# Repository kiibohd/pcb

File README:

PCB and PCB Related Bits

In general kicad is used for projects.
A project will be explicit if another program is required to view.

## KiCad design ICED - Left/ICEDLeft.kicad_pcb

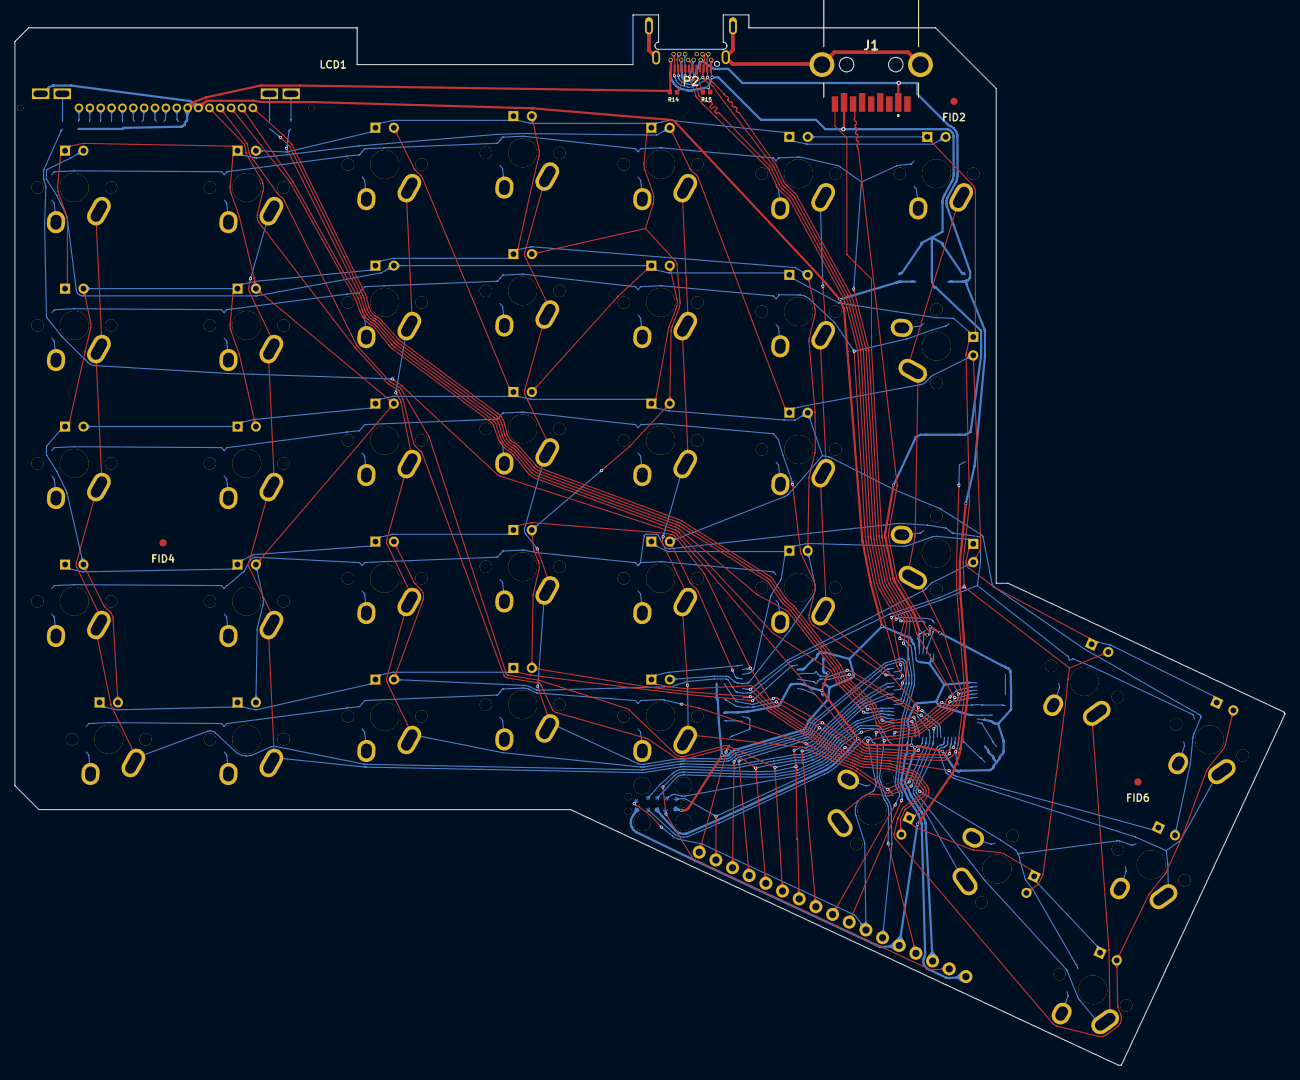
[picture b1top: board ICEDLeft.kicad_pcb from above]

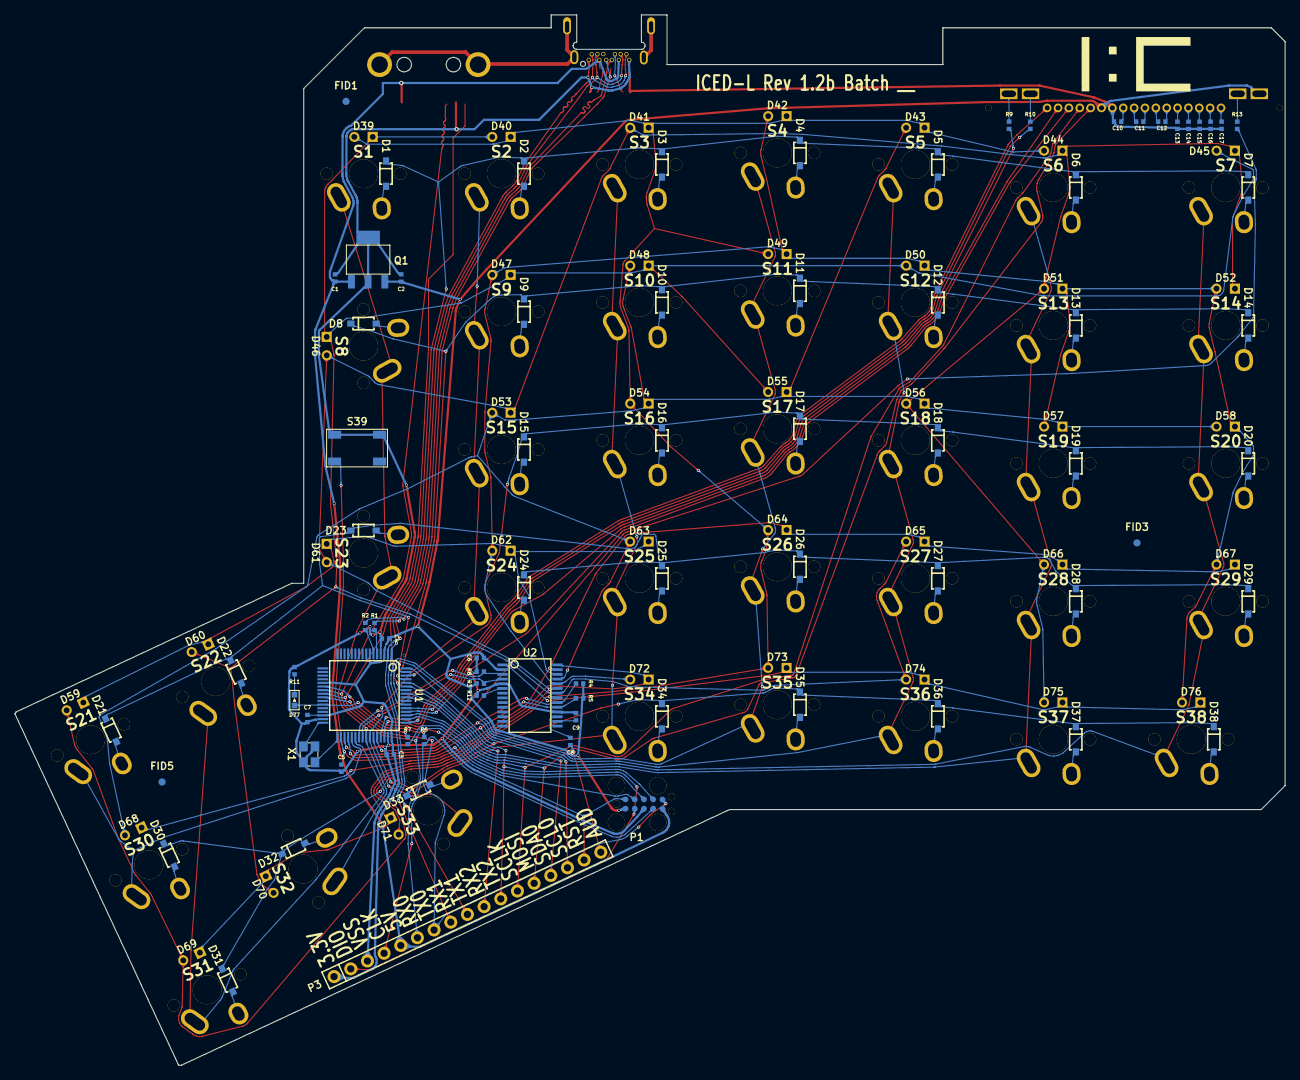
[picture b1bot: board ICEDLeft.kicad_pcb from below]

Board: 2 copper layers, 175.4 x 145.0 mm, 164 parts (80 on the bottom side), 115 nets.

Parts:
C1, C2, C6, C10, C11, C12, C13, C14, C15, C16, C17: 1uF; SMD-1005
C3, C4, C5, C7, C9: 0.1uF; SMD-1005
C8: 0.22uF; SMD-1005
D1, D2, D3, D4, D5, D6, D7, D8, D9, D10, D11, D12, D13, D14, D15, D16, D17, D18, D19, D20, D21, D22, D23, D24, D25, D26, D27, D28, D29, D30, D31, D32, D33, D34, D35, D36, D37, D38: DIODE; SOT123-DIODE
D39, D40, D41, D42, D43, D44, D45, D46, D47, D48, D49, D50, D51, D52, D53, D54, D55, D56, D57, D58, D59, D60, D61, D62, D63, D64, D65, D66, D67, D68, D69, D70, D71, D72, D73, D74, D75, D76: LED; INSW_LEDS_REG
D77: LED; LED-0603
FID1, FID2, FID3, FID4, FID5, FID6: >VALUE; FID
IC_LOGO: IC_LOGO
J1: 692122030100
LCD1: NHD-C12832A1Z
P1: FLASH_HDR; JLINK_NEEDLE
P2: USBC; USB_C_MIDMOUNT_TH_IMPCUT
P3: CONN_17; HEADER_1x17
Q1: TC1264; SOT-223
R1, R2, R13: 33; SMD-1005
R3, R4, R5: 4.7k; SMD-1005
R6, R7: 100; SMD-1005
R8: 100k; SMD-1005
R9, R10: 66.5; SMD-1005
R11: 1k; SMD-1005
R12: 20k; SMD-1005
R14, R15: 5.1k; SMD-1005
S1, S2, S3, S4, S5, S6, S7, S8, S9, S10, S11, S12, S13, S14, S15, S16, S17, S18, S19, S20, S21, S22, S23, S24, S25, S26, S27, S28, S29, S30, S31, S32, S33, S34, S35, S36, S37, S38: SW; MXALPS
S39: TAC_SWITCH; TACT_5.2x5.2
U1: MK20DX256VLH7; LQFP64
U2: IS31FL3731C; SSOP-28
X1: CRYSTAL; NX3225SA

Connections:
+5V: C1.1, J1.1, P1.5, P2.4, P2.9, P2.16, P2.21, P3.5, Q1.1
/Col1: S21.1, S30.1, U1.37
/Col2: S22.1, S31.1, U1.38
/Col3: S1.1, S8.1, S23.1, S32.1, U1.41
/Col4: S2.1, S9.1, S15.1, S24.1, S33.1, U1.42
/Col5: S3.1, S10.1, S16.1, S25.1, S34.1, U1.43
/Col6: S4.1, S11.1, S17.1, S26.1, S35.1, U1.54
/Col7: S5.1, S12.1, S18.1, S27.1, S36.1, U1.55
/Col8: S6.1, S13.1, S19.1, S28.1, S37.1, U1.56
/Col9: S7.1, S14.1, S20.1, S29.1, S38.1, U1.57
/GND: J1.MH1, J1.MH2, P2.25
/Row1: D1.2, D2.2, D3.2, D4.2, D5.2, D6.2, D7.2, U1.58
/Row2: D8.2, D9.2, D10.2, D11.2, D12.2, D13.2, D14.2, U1.61
/Row3: D15.2, D16.2, D17.2, D18.2, D19.2, D20.2, U1.62
/Row4: D21.2, D22.2, D23.2, D24.2, D25.2, D26.2, D27.2, D28.2, D29.2, U1.63
/Row5: D30.2, D31.2, D32.2, D33.2, D34.2, D35.2, D36.2, D37.2, D38.2, U1.64
/ledmatrix/CA1: D39.2, D40.1, D41.1, D42.1, D43.1, D44.2, D49.2, D54.2, D59.2, D64.2, D69.2, D73.2, U2.21
/ledmatrix/CA2: D39.1, D40.2, D45.2, D46.1, D47.1, D48.1, D50.2, D55.2, D60.2, D65.2, D70.2, D74.2, U2.22
/ledmatrix/CA3: D41.2, D44.1, D45.1, D46.2, D51.2, D52.1, D53.1, D56.2, D61.2, D66.2, D71.2, D75.2, U2.23
/ledmatrix/CA4: D42.2, D47.2, D49.1, D50.1, D51.1, D52.2, D57.2, D58.1, D62.2, D67.2, D72.2, D76.2, U2.24
/ledmatrix/CA5: D43.2, D48.2, D53.2, D54.1, D55.1, D56.1, D57.1, D58.2, D63.2, D68.2, U2.25
/ledmatrix/CA6: D59.1, D60.1, D61.1, D62.1, D63.1, U2.26
/ledmatrix/CA7: D64.1, D65.1, D66.1, D67.1, D68.1, U2.27
/ledmatrix/CA8: D69.1, D70.1, D71.1, D72.1, U2.28
/ledmatrix/CA9: D73.1, D74.1, D75.1, D76.1, U2.1
/mcu/A0: LCD1.17, U1.52
/mcu/AUD: C8.2, P3.17
/mcu/INTB: R3.2, U1.40, U2.4
/mcu/LCD_KB: R9.2, U1.46
/mcu/LCD_KG: R10.2, U1.45
/mcu/LCD_KR: R13.2, U1.44
/mcu/MCU_RESET: C5.1, P1.10, P3.16, S39.2, U1.34
/mcu/MOSI: LCD1.15, P3.13, U1.51
/mcu/PTA5: D77.1, P1.9, U1.27
/mcu/RST: LCD1.18, U1.53
/mcu/RX0: J1.6, P1.8, P3.6, U1.23
/mcu/RX1: P2.3, P2.10, P2.15, P2.22, P3.8, U1.2
/mcu/RX2: P3.10, U1.59
/mcu/SCL0: P3.15, R4.2, U1.35, U2.20
/mcu/SCLK: LCD1.16, P3.12, U1.50
/mcu/SDA0: P3.14, R5.2, U1.36, U2.19
/mcu/SDB: R8.2, U1.39, U2.3
/mcu/SS1: LCD1.19, U1.49
/mcu/SWD_CLK: P1.4, P3.4, R6.2
/mcu/SWD_DIO: P1.2, P3.2, R7.2
/mcu/TX0: J1.5, P1.6, P3.7, U1.24
/mcu/TX1: P2.2, P2.11, P2.14, P2.23, P3.9, U1.1
/mcu/TX2: P1.7, P3.11, U1.60
/mcu/USB_DM: P2.7, P2.19, R2.1
/mcu/USB_DP: P2.6, P2.18, R1.1
unnamed: C8.1, U2.17
unnamed: C9.1, U2.16
unnamed: C10.1, LCD1.12
unnamed: C11.1, LCD1.11
unnamed: C11.2, LCD1.10
unnamed: C12.1, LCD1.9
unnamed: C12.2, LCD1.8
unnamed: C13.2, LCD1.7
unnamed: C14.2, LCD1.6
unnamed: C15.2, LCD1.5
unnamed: C16.2, LCD1.4
unnamed: C17.2, LCD1.3
unnamed: D1.1, S1.2
unnamed: D2.1, S2.2
unnamed: D3.1, S3.2
unnamed: D4.1, S4.2
unnamed: D5.1, S5.2
unnamed: D6.1, S6.2
unnamed: D7.1, S7.2
unnamed: D8.1, S8.2
unnamed: D9.1, S9.2
unnamed: D10.1, S10.2
unnamed: D11.1, S11.2
unnamed: D12.1, S12.2
unnamed: D13.1, S13.2
unnamed: D14.1, S14.2
unnamed: D15.1, S15.2
unnamed: D16.1, S16.2
unnamed: D17.1, S17.2
unnamed: D18.1, S18.2
unnamed: D19.1, S19.2
unnamed: D20.1, S20.2
unnamed: D21.1, S21.2
unnamed: D22.1, S22.2
unnamed: D23.1, S23.2
unnamed: D24.1, S24.2
unnamed: D25.1, S25.2
unnamed: D26.1, S26.2
unnamed: D27.1, S27.2
unnamed: D28.1, S28.2
unnamed: D29.1, S29.2
unnamed: D30.1, S30.2
unnamed: D31.1, S31.2
unnamed: D32.1, S32.2
unnamed: D33.1, S33.2
unnamed: D34.1, S34.2
unnamed: D35.1, S35.2
unnamed: D36.1, S36.2
unnamed: D37.1, S37.2
unnamed: D38.1, S38.2
unnamed: D77.2, R11.1
unnamed: LCD1.2, R13.1
unnamed: LCD1.20, R10.1
unnamed: LCD1.21, R9.1
unnamed: P2.5, R15.1
unnamed: P2.17, R14.1
unnamed: R1.2, U1.5
unnamed: R2.2, U1.6
unnamed: R6.1, U1.22
unnamed: R7.1, U1.25
unnamed: R12.1, U2.6
unnamed: U1.32, X1.1
unnamed: U1.33, X1.3
VDD: C2.1, C3.1, C4.1, C6.2, C7.1, LCD1.1, LCD1.14, P1.1, P3.1, Q1.3, R3.1, R4.1, R5.1, U1.3, U1.7, U1.8, U1.21, U1.30, U1.48, U2.2
VSS: C1.2, C2.2, C3.2, C4.2, C5.2, C6.1, C7.2, C9.2, C10.2, C13.1, C14.1, C15.1, C16.1, C17.1, J1.4, LCD1.13, P1.3, P2.1, P2.12, P2.13, P2.24, P3.3, Q1.2, R8.1, R11.2, R12.2, R14.2, R15.2, S39.3, S39.4, U1.4, U1.31, U1.47, U2.5, U2.18, X1.2, X1.4

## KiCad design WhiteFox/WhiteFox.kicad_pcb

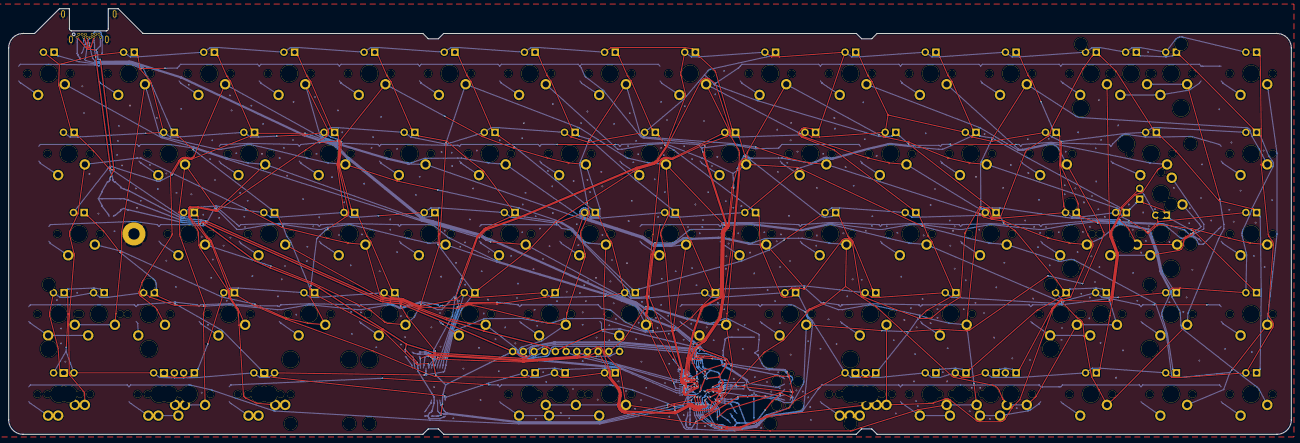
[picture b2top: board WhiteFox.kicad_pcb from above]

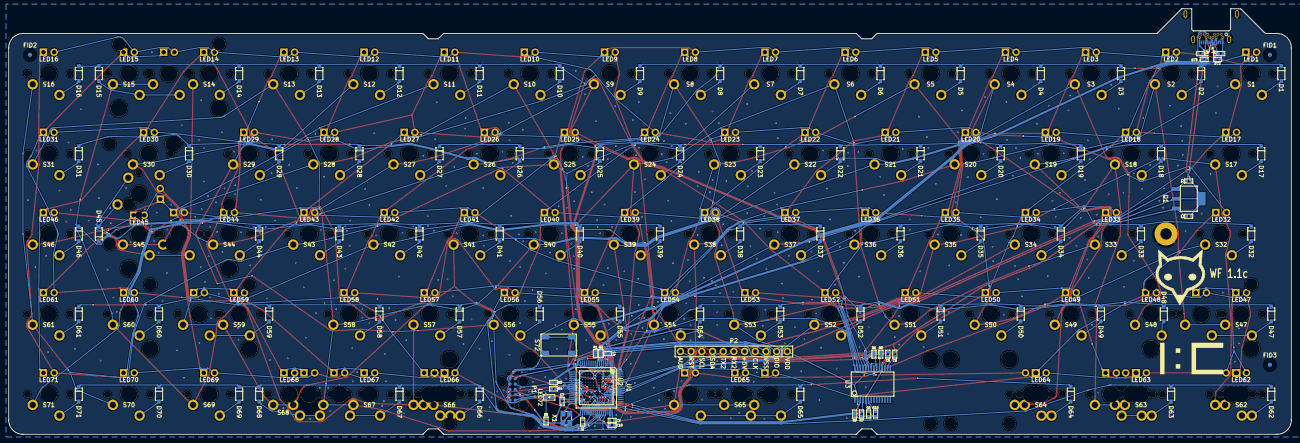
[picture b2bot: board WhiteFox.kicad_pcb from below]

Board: 2 copper layers, 304.8 x 101.1 mm, 297 parts (109 on the bottom side), 128 nets.

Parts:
C1, C2, C6: 1uF; SMD-0402
C3, C4, C5, C7, C9, C10: 0.1uF; SMD-0402
C8: 0.22uF; SMD-0402
D1, D2, D3, D4, D5, D6, D7, D8, D9, D10, D11, D12, D13, D14, D15, D16, D17, D18, D19, D20, D21, D22, D23, D24, D25, D26, D27, D28, D29, D30, D31, D32, D33, D34, D35, D36, D37, D38, D39, D40, D41, D42, D43, D44, D45, D46, D47, D48, D49, D50, D51, D52, D53, D54, D55, D56, D57, D58, D59, D60, D61, D62, D63, D64, D65, D66, D67, D68, D69, D70, D71: DIODE; SOT123-DIODE
D72, D73: ESD_BIDIR_1CH; SMD-0402
FID1, FID2, FID3: >VALUE; FID
H1: 1PIN; 1PAD_5.5
IC_LOGO: IC_LOGO
J1: USBC; E8124-010-01
LED1, LED2, LED3, LED4, LED5, LED6, LED7, LED8, LED9, LED10, LED11, LED12, LED13, LED14, LED15, LED16, LED17, LED18, LED19, LED20, LED21, LED22, LED23, LED24, LED25, LED26, LED27, LED28, LED29, LED30, LED31, LED32, LED33, LED34, LED35, LED36, LED37, LED38, LED39, LED40, LED41, LED42, LED43, LED44, LED45, LED46, LED47, LED48, LED49, LED50, LED51, LED52, LED53, LED54, LED55, LED56, LED57, LED58, LED59, LED60, LED61, LED62, LED63, LED64, LED65, LED66, LED67, LED68, LED69, LED70, LED71: LED; INSW_LEDS
LED72: LED; LED-0603
LED115, LED145, LED147, LED159, LED162, LED163, LED164, LED165, LED166, LED167, LED168, LED245, LED263, LED265, LED266: LED; INSW_LEDS_HIDDEN
P1: FLASH_HDR; JLINK_NEEDLE
P2: CONN_11; HEADER_1x11
Q1: TC1264; SOT-223
R1, R2: 33; SMD-0402
R3, R4: 100; SMD-0402
R5, R6, R7: 4.7k; SMD-0402
R8: 1k; SMD-0402
R9: 100k; SMD-0402
R10: 20k; SMD-0402
R11, R12: 5.1k; SMD-0402
S1, S2, S3, S4, S5, S6, S7, S8, S9, S10, S11, S12, S13, S14, S15, S16, S17, S18, S19, S20, S21, S22, S23, S24, S25, S26, S27, S28, S29, S30, S31, S32, S33, S34, S35, S36, S37, S38, S39, S40, S41, S42, S43, S44, S45, S46, S47, S48, S49, S50, S51, S52, S53, S54, S55, S56, S57, S58, S59, S60, S61, S62, S63, S64, S65, S66, S67, S68, S69, S70, S71: SW; MX
S72: TAC_SWITCH; TACT_5.2x5.2
S115, S145, S147, S159, S162, S163, S164, S165, S166, S167, S168, S245, S263, S265, S266: SW; MX_HIDDEN
STAB1, STAB2, STAB3, STAB4, STAB5, STAB6, STAB7, STAB8, STAB9, STAB10, STAB11, STAB12, STAB13, STAB14, STAB15: STAB
U1: MK20DX256VLH7; LQFP64
U2: MK20DX256VMC7R; MAPBGA121
U3: IS31FL3731C; SSOP-28
X1: CRYSTAL; NX3225SA

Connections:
+5V: C1.1, J1.4, J1.9, J1.16, J1.21, P1.5, P2.5, Q1.1
/Col1: S1.1, S10.1, S19.1, S28.1, S37.1, S46.1, S55.1, S64.1, S164.1, U1.37, U2.G9
/Col2: S2.1, S11.1, S20.1, S29.1, S38.1, S47.1, S56.1, S65.1, S147.1, S165.1, S265.1, U1.38, U2.G8
/Col3: S3.1, S12.1, S21.1, S30.1, S39.1, S48.1, S57.1, S66.1, S166.1, S266.1, U1.41, U2.D9
/Col4: S4.1, S13.1, S22.1, S31.1, S40.1, S49.1, S58.1, S67.1, S167.1, U1.42, U2.C9
/Col5: S5.1, S14.1, S23.1, S32.1, S41.1, S50.1, S59.1, S68.1, S159.1, S168.1, U1.43, U2.B9
/Col6: S6.1, S15.1, S24.1, S33.1, S42.1, S51.1, S60.1, S69.1, S115.1, U1.53, U2.A7
/Col7: S7.1, S16.1, S25.1, S34.1, S43.1, S52.1, S61.1, S70.1, U1.54, U2.D6
/Col8: S8.1, S17.1, S26.1, S35.1, S44.1, S53.1, S62.1, S71.1, S162.1, U1.55, U2.C6
/Col9: S9.1, S18.1, S27.1, S36.1, S45.1, S54.1, S63.1, S145.1, S163.1, S245.1, S263.1, U1.56, U2.C5
/Row1: D1.2, D2.2, D3.2, D4.2, D5.2, D6.2, D7.2, D8.2, D9.2, U1.57, U2.D4
/Row2: D10.2, D11.2, D12.2, D13.2, D14.2, D15.2, D16.2, D17.2, D18.2, U1.58, U2.D3
/Row3: D19.2, D20.2, D21.2, D22.2, D23.2, D24.2, D25.2, D26.2, D27.2, U1.61, U2.A3
/Row4: D28.2, D29.2, D30.2, D31.2, D32.2, D33.2, D34.2, D35.2, D36.2, U1.62, U2.A2
/Row5: D37.2, D38.2, D39.2, D40.2, D41.2, D42.2, D43.2, D44.2, D45.2, U1.63, U2.B2
/Row6: D46.2, D47.2, D48.2, D49.2, D50.2, D51.2, D52.2, D53.2, D54.2, U1.64, U2.A1
/Row7: D55.2, D56.2, D57.2, D58.2, D59.2, D60.2, D61.2, D62.2, D63.2, U1.44, U2.D8
/Row8: D64.2, D65.2, D66.2, D67.2, D68.2, D69.2, D70.2, D71.2, U1.45, U2.C8
/ledmatrix/CA1: LED1.2, LED2.2, LED3.2, LED4.2, LED5.2, LED6.2, LED7.2, LED8.2, LED9.1, LED17.1, LED25.1, LED33.1, LED41.1, LED49.1, LED57.1, LED65.1, LED165.1, LED265.1, U3.21
/ledmatrix/CA2: LED1.1, LED9.2, LED10.2, LED11.2, LED12.2, LED13.2, LED14.2, LED15.2, LED16.2, LED18.1, LED26.1, LED34.1, LED42.1, LED50.1, LED58.1, LED66.1, LED115.2, LED166.1, LED266.1, U3.22
/ledmatrix/CA3: LED2.1, LED10.1, LED17.2, LED18.2, LED19.2, LED20.2, LED21.2, LED22.2, LED23.2, LED24.2, LED27.1, LED35.1, LED43.1, LED51.1, LED59.1, LED67.1, LED159.1, LED167.1, U3.23
/ledmatrix/CA4: LED3.1, LED11.1, LED19.1, LED25.2, LED26.2, LED27.2, LED28.2, LED29.2, LED30.2, LED31.2, LED32.2, LED36.1, LED44.1, LED52.1, LED60.1, LED68.1, LED168.1, U3.24
/ledmatrix/CA5: LED4.1, LED12.1, LED20.1, LED28.1, LED33.2, LED34.2, LED35.2, LED36.2, LED37.2, LED38.2, LED39.2, LED40.2, LED45.1, LED53.1, LED61.1, LED69.1, LED145.1, LED245.1, U3.25
/ledmatrix/CA6: LED5.1, LED13.1, LED21.1, LED29.1, LED37.1, LED41.2, LED42.2, LED43.2, LED44.2, LED45.2, LED46.2, LED47.2, LED48.2, LED54.1, LED62.1, LED70.1, LED145.2, LED147.2, LED162.1, LED245.2, U3.26
/ledmatrix/CA7: LED6.1, LED14.1, LED22.1, LED30.1, LED38.1, LED46.1, LED49.2, LED50.2, LED51.2, LED52.2, LED53.2, LED54.2, LED55.2, LED56.2, LED63.1, LED71.1, LED163.1, LED263.1, U3.27
/ledmatrix/CA8: LED7.1, LED15.1, LED23.1, LED31.1, LED39.1, LED47.1, LED55.1, LED57.2, LED58.2, LED59.2, LED60.2, LED61.2, LED62.2, LED63.2, LED64.2, LED115.1, LED147.1, LED159.2, LED162.2, LED163.2, LED164.2, LED263.2, U3.28
/ledmatrix/CA9: LED8.1, LED16.1, LED24.1, LED32.1, LED40.1, LED48.1, LED56.1, LED64.1, LED65.2, LED66.2, LED67.2, LED68.2, LED69.2, LED70.2, LED71.2, LED164.1, LED165.2, LED166.2, LED167.2, LED168.2, LED265.2, LED266.2, U3.1
/mcu/AUD: C8.2, P2.11
/mcu/EXTAL0: U1.32, U2.L11, X1.1
/mcu/INTB: R7.2, U1.40, U2.E9, U3.4
/mcu/MCU_RESET: C5.1, P1.10, P2.10, S72.2, U1.34, U2.J11
/mcu/PTA0: R3.1, U1.22, U2.J6
/mcu/PTA3: R4.1, U1.25, U2.H9
/mcu/PTA5: LED72.1, P1.9, U1.27, U2.K7
/mcu/RX0: P1.8, U1.23, U2.H8
/mcu/RX2: P2.6, U1.59, U2.C3
/mcu/SCL0: P2.9, R6.2, U1.35, U2.G11, U3.20
/mcu/SDA0: P2.8, R5.2, U1.36, U2.G10, U3.19
/mcu/SDB: R9.2, U1.39, U2.B10, U3.3
/mcu/SHLD: H1.1, J1.25
/mcu/SWD_CLK: P1.4, P2.4, R3.2
/mcu/SWD_DIO: P1.2, P2.2, R4.2
/mcu/TX0: P1.6, U1.24, U2.J7
/mcu/TX2: P1.7, P2.7, U1.60, U2.B3
/mcu/USB0_DM: R1.2, U1.6, U2.F2
/mcu/USB0_DP: R2.2, U1.5, U2.F1
/mcu/USB_DM: D73.1, J1.7, J1.19, R1.1
/mcu/USB_DP: D72.1, J1.6, J1.18, R2.1
/mcu/XTAL0: U1.33, U2.K11, X1.3
unnamed: C8.1, U3.17
unnamed: C9.1, U3.16
unnamed: D1.1, S1.2
unnamed: D2.1, S2.2
unnamed: D3.1, S3.2
unnamed: D4.1, S4.2
unnamed: D5.1, S5.2
unnamed: D6.1, S6.2
unnamed: D7.1, S7.2
unnamed: D8.1, S8.2
unnamed: D9.1, S9.2
unnamed: D10.1, S10.2
unnamed: D11.1, S11.2
unnamed: D12.1, S12.2
unnamed: D13.1, S13.2
unnamed: D14.1, S14.2
unnamed: D15.1, S15.2, S115.2
unnamed: D16.1, S16.2
unnamed: D17.1, S17.2
unnamed: D18.1, S18.2
unnamed: D19.1, S19.2
unnamed: D20.1, S20.2
unnamed: D21.1, S21.2
unnamed: D22.1, S22.2
unnamed: D23.1, S23.2
unnamed: D24.1, S24.2
unnamed: D25.1, S25.2
unnamed: D26.1, S26.2
unnamed: D27.1, S27.2
unnamed: D28.1, S28.2
unnamed: D29.1, S29.2
unnamed: D30.1, S30.2
unnamed: D31.1, S31.2
unnamed: D32.1, S32.2
unnamed: D33.1, S33.2
unnamed: D34.1, S34.2
unnamed: D35.1, S35.2
unnamed: D36.1, S36.2
unnamed: D37.1, S37.2
unnamed: D38.1, S38.2
unnamed: D39.1, S39.2
unnamed: D40.1, S40.2
unnamed: D41.1, S41.2
unnamed: D42.1, S42.2
unnamed: D43.1, S43.2
unnamed: D44.1, S44.2
unnamed: D45.1, S45.2, S145.2, S245.2
unnamed: D46.1, S46.2
unnamed: D47.1, S47.2, S147.2
unnamed: D48.1, S48.2
unnamed: D49.1, S49.2
unnamed: D50.1, S50.2
unnamed: D51.1, S51.2
unnamed: D52.1, S52.2
unnamed: D53.1, S53.2
unnamed: D54.1, S54.2
unnamed: D55.1, S55.2
unnamed: D56.1, S56.2
unnamed: D57.1, S57.2
unnamed: D58.1, S58.2
unnamed: D59.1, S59.2, S159.2
unnamed: D60.1, S60.2
unnamed: D61.1, S61.2
unnamed: D62.1, S62.2, S162.2
unnamed: D63.1, S63.2, S163.2, S263.2
unnamed: D64.1, S64.2, S164.2
unnamed: D65.1, S65.2, S165.2, S265.2
unnamed: D66.1, S66.2, S166.2, S266.2
unnamed: D67.1, S67.2, S167.2
unnamed: D68.1, S68.2, S168.2
unnamed: D69.1, S69.2
unnamed: D70.1, S70.2
unnamed: D71.1, S71.2
unnamed: J1.5, R12.1
unnamed: J1.17, R11.2
unnamed: LED72.2, R8.1
unnamed: R10.1, U3.6
VDD: C2.1, C3.1, C4.1, C6.2, C7.1, C10.1, P1.1, P2.1, Q1.3, R5.1, R6.1, R7.1, U1.3, U1.7, U1.8, U1.21, U1.30, U1.48, U2.E5, U2.E6, U2.E7, U2.G1, U2.G2, U2.K6, U2.L10, U3.2
VSS: C1.2, C2.2, C3.2, C4.2, C5.2, C6.1, C7.2, C9.2, C10.2, D72.2, D73.2, J1.1, J1.12, J1.13, J1.24, P1.3, P2.3, Q1.2, R8.2, R9.1, R10.2, R11.1, R12.2, S72.3, S72.4, U1.4, U1.31, U1.47, U2.F7, U2.G3, U2.G7, U2.K10, U2.L6, U3.5, U3.18, X1.2, X1.4

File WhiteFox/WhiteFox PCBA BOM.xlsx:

# | Quantity | PCB Part Reference | Supplier PN | Manufacturer | Description | Package | Notes
1 | 3 | C1,C2,C6 | JMK105C6105KV-F | Taiyo Yuden | Multilayer Ceramic Capacitors MLCC - SMD/SMT 1uF 6.3V X6S +/-10% 0402 Gen Purp | SMD-0402
2 | 5 | C3,C4,C5,C7,C9,C10 | EMK105B7104KV-F | Taiyo Yuden | Multilayer Ceramic Capacitors MLCC - SMD/SMT 0.1uF 16V X7R +/-10% 0402 Gen Purp | SMD-0402
3 | 1 | C8 | JMK105B7224KV-F | Taiyo Yuden | Multilayer Ceramic Capacitors MLCC - SMD/SMT 0.22uF 6.3V X7R +/-10% 0402 Gen Pu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 | SMD-0402
4 | 71 | D1-D71 | 1N4148W-TP | Micro Commercial Components | Diodes - General Purpose, Power, Switching 300mA, 100V | SOT123-DIODE
5 | 2 | D72,D73 | LXES15AAA1-133 | Murata | ESD Suppressors / TVS Diodes 15 VDC | SMD-0402
6 | 1 | J1 | E8124-010-01 | Pulse Electronics | USB Connectors USB 3.1 TYPE C 5G Mid Mount | USBC
7 | 1 | LED72 | LO Q976-PS-25 | Osram Opto Semiconductor | Standard LEDs - SMD Orange, 605nm 280mcd, 20mA | LED-0603
8 | 1 | Q1 | TC1264-3.3VDB | Microchip | LDO Voltage Regulators 800mA Fixed Output CMOS LDO | SOT-223
9 | 2 | R1,R2 | RK73B1ETTP330J | KOA Speer | Thick Film Resistors - SMD 1/16watts 33ohms 5% | SMD-0402
10 | 2 | R3,R4 | RK73B1ETTP101J | KOA Speer | Thick Film Resistors - SMD 1/16watts 100ohms 5% | SMD-0402
11 | 3 | R5,R6,R7 | RK73B1ETTP472J | KOA Speer | Thick Film Resistors - SMD 0.1W 4.7Kohms 5% | SMD-0402
12 | 1 | R8 | RK73B1ETTP102J | KOA Speer | Thick Film Resistors - SMD 1/16watts 1Kohms 5% | SMD-0402
13 | 1 | R9 | RK73B1ETTP104J | KOA Speer | Thick Film Resistors - SMD 1/16watt 100Kohms 5% | SMD-0402
14 | 1 | R10 | RK73B1ETTP203J | KOA Speer | Thick Film Resistors - SMD 0.1W 20Kohms 5% | SMD-0402
15 | 2 | R11,R12 | RK73B1ETTP512J | KOA Speer | Thick Film Resistors - SMD 1/16watt 5.1Kohms 5% | SMD-0402
16 | 1 | S72 | SKQGAKE010 | ALPS | Tactile Switches 50 mAmps at 12 Volts | TACT_5.2x5.2
17 | 1 | U1 | MK20DX256VLH7 | NXP / Freescale | ARM Microcontrollers - MCU KINETIS 256K | LQFP64 | Alternative to U1. Populate this OR U2.
18 | 1 | U2 | MK20DX256VMC7R | NXP / Freescale | ARM Microcontrollers - MCU KINETIS 256K | MAPBGA121 | Alternative to U2. Populate this OR U1. MK20DX256VMC7 is non-reel PN.
19 | 1 | U3 | IS31FL3731C-SALS2 | ISSI | LED Lighting Drivers Audio Mod 144 Dot LED Driver, SSOP-28 | SSOP-28
20 | 1 | X1 | NX3225SA-16.000M-STD-CSR-1 | NDK | CRYSTAL 16.0000MHZ 8PF SMD | NX3225SA | NX3225SA-16.000M-STD-CSR-3 or CX3225GB16000D0HPQCC can be substituted.

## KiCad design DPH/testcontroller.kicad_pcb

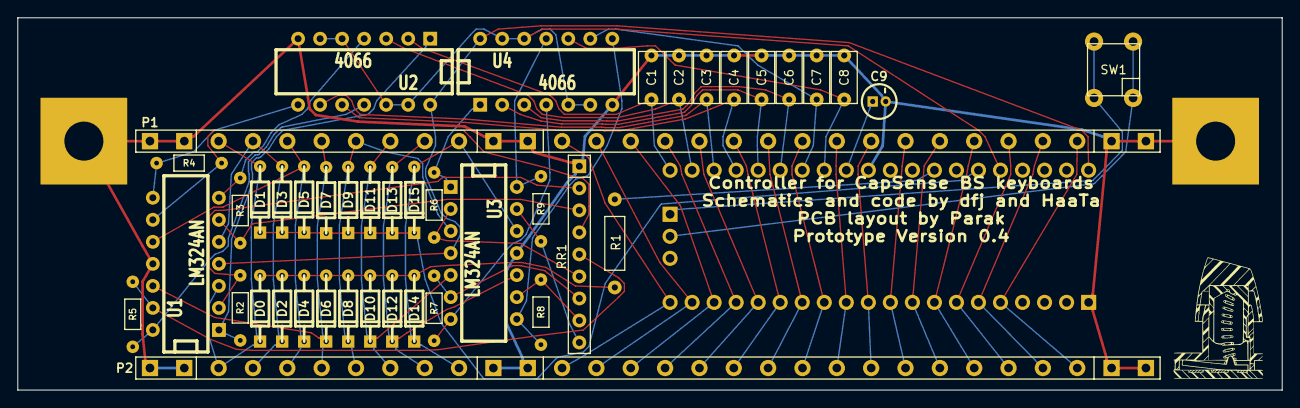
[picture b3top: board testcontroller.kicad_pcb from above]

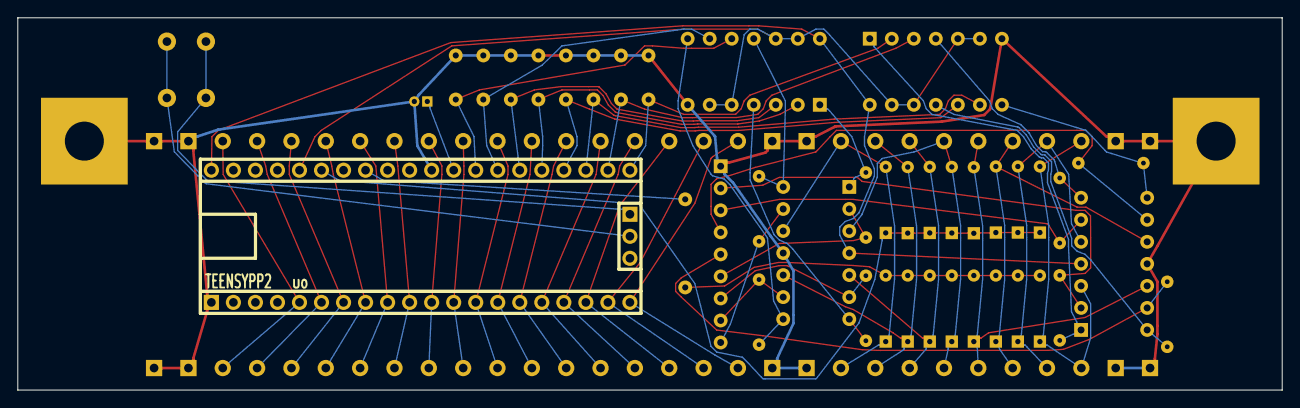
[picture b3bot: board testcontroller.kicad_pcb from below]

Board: 2 copper layers, 145.8 x 42.9 mm, 46 parts (2 on the bottom side), 57 nets.

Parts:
C1, C2, C3, C4, C5, C6, C7, C8: 500pF; CAPACITOR_DISC_6MM_3MM
C9: 1uF; CAPACITOR_ELE_4MM_1.5MM
D0, D1, D2, D3, D4, D5, D6, D7, D8, D9, D10, D11, D12, D13, D14, D15: DIODE; DO-35
P1, P2: MODELF_CONN30; PIN_ARRAY-30X1
P4, P5: 1PAD; GND_SCREW_PAD
R1: 47K; RESISTOR_6.2MM_2.3MM
R2, R3, R4, R5, R6, R7, R8, R9: 36K; RESISTOR_3.5MM_1.85MM
RR1: 10K; RESISTOR_NETWORK_9
SW1: SW_PUSH_4PIN; BUTTON_TACT_6x6MM
U0: TEENSYPP2; TEENSYPP2_NOINT2
U1, U3: LM324AN; DIP-14__300
U2, U4: 4066; DIP-14__300
VAL: LOGO

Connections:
+5V: U0.52, U1.4, U2.14, U3.4, U4.14
/ADC_0: C1.1, U0.33, U2.2
/ADC_1: C2.1, U0.34, U2.3
/ADC_2: C3.1, U0.35, U2.9
/ADC_3: C4.1, U0.36, U2.10
/ADC_4: C5.1, U0.37, U4.2
/ADC_5: C6.1, U0.38, U4.3
/ADC_6: C7.1, U0.39, U4.9
/ADC_7: C8.1, U0.40, U4.10
/AREF: C9.1, U0.41
/HOLD_CTRL: U0.48, U2.5, U2.6, U2.12, U2.13, U4.5, U4.6, U4.12, U4.13
/RESET: SW1.3, SW1.4, U0.23
/RST_GND: SW1.1, SW1.2, U0.22
/SENSE_0: D0.2, D1.1, P1.3, P2.3, U1.3
/SENSE_1: D2.2, D3.1, P1.4, P2.4, U1.5
/SENSE_2: D4.2, D5.1, P1.5, P2.5, U1.10
/SENSE_3: D6.2, D7.1, P1.6, P2.6, U1.12
/SENSE_4: D8.2, D9.1, P1.7, P2.7, U3.3
/SENSE_5: D10.2, D11.1, P1.8, P2.8, U3.5
/SENSE_6: D12.2, D13.1, P1.9, P2.9, U3.10
/SENSE_7: D14.2, D15.1, P1.10, P2.10, U3.12
/SR0: R2.1, RR1.2, U1.2
/SR1: R3.1, RR1.3, U1.6
/SR2: R4.1, RR1.4, U1.9
/SR3: R5.1, RR1.5, U1.13
/SR4: R6.1, RR1.6, U3.2
/SR5: R7.1, RR1.7, U3.6
/SR6: R8.1, RR1.8, U3.9
/SR7: R9.1, RR1.9, U3.13
/STAB_HIGH: R1.1, U0.45
/STAB_LOW: D1.2, D3.2, D5.2, D7.2, D9.2, D11.2, D13.2, D15.2, U0.47
/STROBE_0: P1.13, P2.13, U0.20
/STROBE_1: P1.14, P2.14, U0.19
/STROBE_2: P1.15, P2.15, U0.18
/STROBE_3: P1.16, P2.16, U0.17
/STROBE_4: P1.17, P2.17, U0.16
/STROBE_5: P1.18, P2.18, U0.15
/STROBE_6: P1.19, P2.19, U0.14
/STROBE_7: P1.20, P2.20, U0.13
/STROBE_8: P1.21, P2.21, U0.12
/STROBE_9: P1.22, P2.22, U0.11
/STROBE_10: P1.23, P2.23, U0.10
/STROBE_11: P1.24, P2.24, U0.9
/STROBE_12: P1.25, P2.25, U0.8
/STROBE_13: P1.26, P2.26, U0.7
/STROBE_14: P1.27, P2.27, U0.6
/STROBE_15: P1.28, P2.28, U0.5
GND: C1.2, C2.2, C3.2, C4.2, C5.2, C6.2, C7.2, C8.2, C9.2, P1.1, P1.2, P1.11, P1.12, P1.29, P1.30, P2.1, P2.2, P2.11, P2.12, P2.29, P2.30, P4.1, P5.1, RR1.1, U0.1, U0.42, U1.11, U2.7, U3.11, U4.7
unnamed: D0.1, D2.1, D4.1, D6.1, D8.1, D10.1, D12.1, D14.1, R1.2
unnamed: R4.2, U1.8, U2.8
unnamed: R9.2, U3.14, U4.11
unnamed: R2.2, U1.1, U2.1
unnamed: R5.2, U1.14, U2.11
unnamed: R8.2, U3.8, U4.8
unnamed: R3.2, U1.7, U2.4
unnamed: R6.2, U3.1, U4.1
unnamed: R7.2, U3.7, U4.4

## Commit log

2014-09-24 initial
2015-02-14 Tweak the mk20 schematic to reflect correct pins
2015-02-14 Adding CERN License
2015-02-14 Converting README to use markdown
2015-02-14 Update schematic sheet details
2015-02-15 Update pcb sheet details
2015-02-27 Add a pdf of the schematic.
2015-09-03 Add DPH controller board and schematics. Works as is, but could use a number of tweaks and improvements...
2015-09-11 Interim update to 1.03
2015-09-11 Remove autosave
2015-09-11 Rename Massdrop1 to IC60 and update to 1.03a. Changes are mostly a new usb connector and extra switch position.
2015-09-11 Remove unneeded footprints and tweak the netlist a bit to fix for the correct new usb module.
2015-10-09 Add Infinity Ergodox.
2015-10-31 Fix (remove invalid LEDs) and prettify the BOM a bit.
2016-06-11 Add WhiteFox.
2016-07-20 IC60 1.1a, now with moar LEDs.
2016-07-20 Update readme slightly.
2016-08-02 Adding IRC link
2016-10-16 ICED 1.2b, now with 100% more Type C
2017-11-03 Add K-Type.
2017-11-03 Adding readme info
2018-03-14 Unless otherwise specified we've always used the CERN Open Hardware License v1.2
    - This goes back to the original Infinity 60% pcb
    - DPH is CC BY-NC-SA (currently the only exception)
2018-03-25 WhiteFox 1.1c
2019-03-27 Add Kira.
2019-03-27 Adding ship date of Kira
2020-07-27 Update the left USB A connector
